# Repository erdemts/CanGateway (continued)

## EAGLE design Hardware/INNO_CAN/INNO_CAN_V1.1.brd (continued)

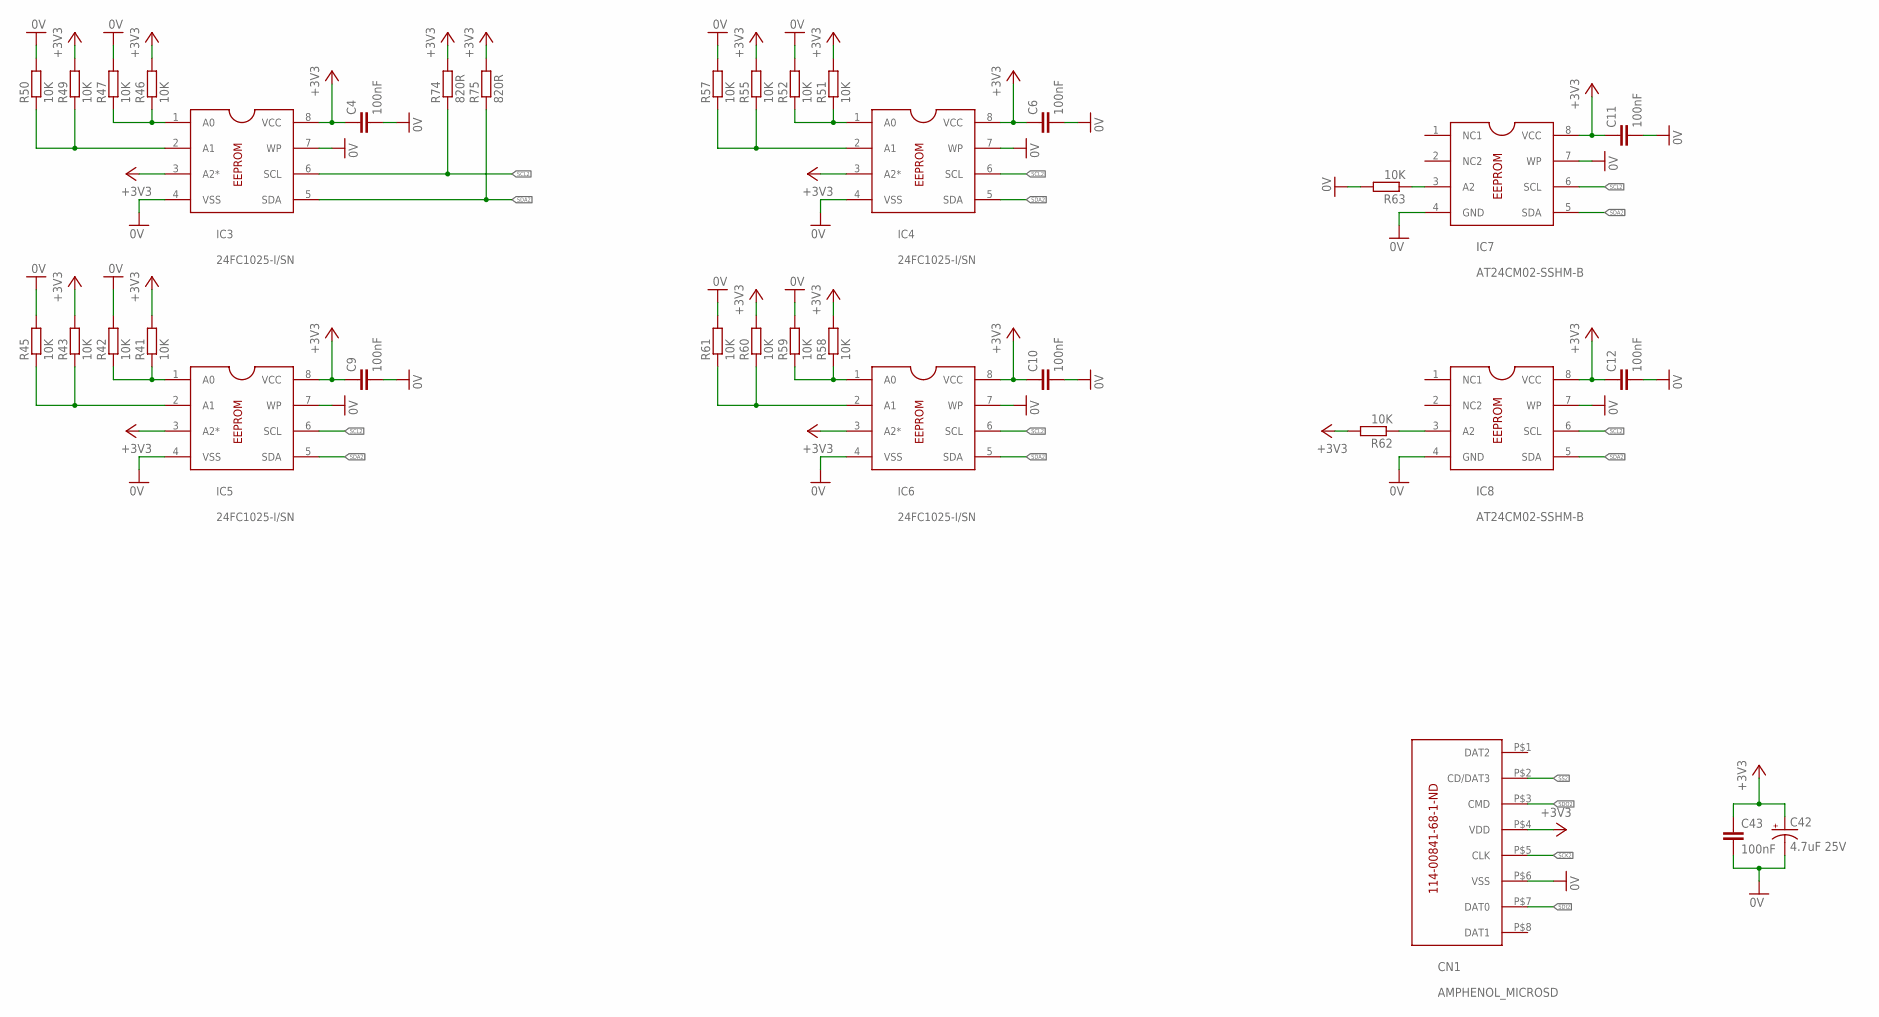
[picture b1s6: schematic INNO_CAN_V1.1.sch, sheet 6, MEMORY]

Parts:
C4, C6, C9, C10, C11, C12, C43: 100nF; C0603
C42: 4.7uF 25V; A/3216-18R
CN1: AMPHENOL_MICROSD
IC3, IC4, IC5, IC6: 24FC1025-I/SN; SOIC08
IC7, IC8: AT24CM02-SSHM-B; SOIC08
R41, R42, R43, R45, R46, R47, R49, R50, R51, R52, R55, R57, R58, R59, R60, R61, R62, R63: 10K; R0603
R74, R75: 820R; R0603

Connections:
0V: C4.2, C6.2, C9.2, C10.2, C11.2, C12.2, C42.-, C43.2, CN1.P$6 (VSS), IC3.4 (VSS), IC3.7 (WP), IC4.4 (VSS), IC4.7 (WP), IC5.4 (VSS), IC5.7 (WP), IC6.4 (VSS), IC6.7 (WP), IC7.4 (GND), IC7.7 (WP), IC8.4 (GND), IC8.7 (WP), R42.2, R45.2, R47.2, R50.2, R52.2, R57.2, R59.2, R61.2, R63.2; also elsewhere on the board
+3V3: C4.1, C6.1, C9.1, C10.1, C11.1, C12.1, C42.+, C43.1, CN1.P$4 (VDD), IC3.3 (A2*), IC3.8 (VCC), IC4.3 (A2*), IC4.8 (VCC), IC5.3 (A2*), IC5.8 (VCC), IC6.3 (A2*), IC6.8 (VCC), IC7.8 (VCC), IC8.8 (VCC), R41.2, R43.2, R46.2, R49.2, R51.2, R55.2, R58.2, R60.2, R62.2, R74.2, R75.2; also elsewhere on the board
unnamed: IC5.1 (A0), R41.1, R42.1
unnamed: IC5.2 (A1), R43.1, R45.1
unnamed: IC3.1 (A0), R46.1, R47.1
unnamed: IC3.2 (A1), R49.1, R50.1
unnamed: IC4.2 (A1), R55.1, R57.1
unnamed: IC4.1 (A0), R51.1, R52.1
unnamed: IC6.1 (A0), R58.1, R59.1
unnamed: IC6.2 (A1), R60.1, R61.1
unnamed: IC8.3 (A2), R62.1
unnamed: IC7.3 (A2), R63.1
SCK2: CN1.P$5 (CLK); also elsewhere on the board
SCL2: IC3.6 (SCL), IC4.6 (SCL), IC5.6 (SCL), IC6.6 (SCL), IC7.6 (SCL), IC8.6 (SCL), R74.1; also elsewhere on the board
SDA2: IC3.5 (SDA), IC4.5 (SDA), IC5.5 (SDA), IC6.5 (SDA), IC7.5 (SDA), IC8.5 (SDA), R75.1; also elsewhere on the board
SDI2: CN1.P$7 (DAT0); also elsewhere on the board
SDO2: CN1.P$3 (CMD); also elsewhere on the board
SS2: CN1.P$2 (CD/DAT3); also elsewhere on the board

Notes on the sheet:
114-00841-68-1-ND

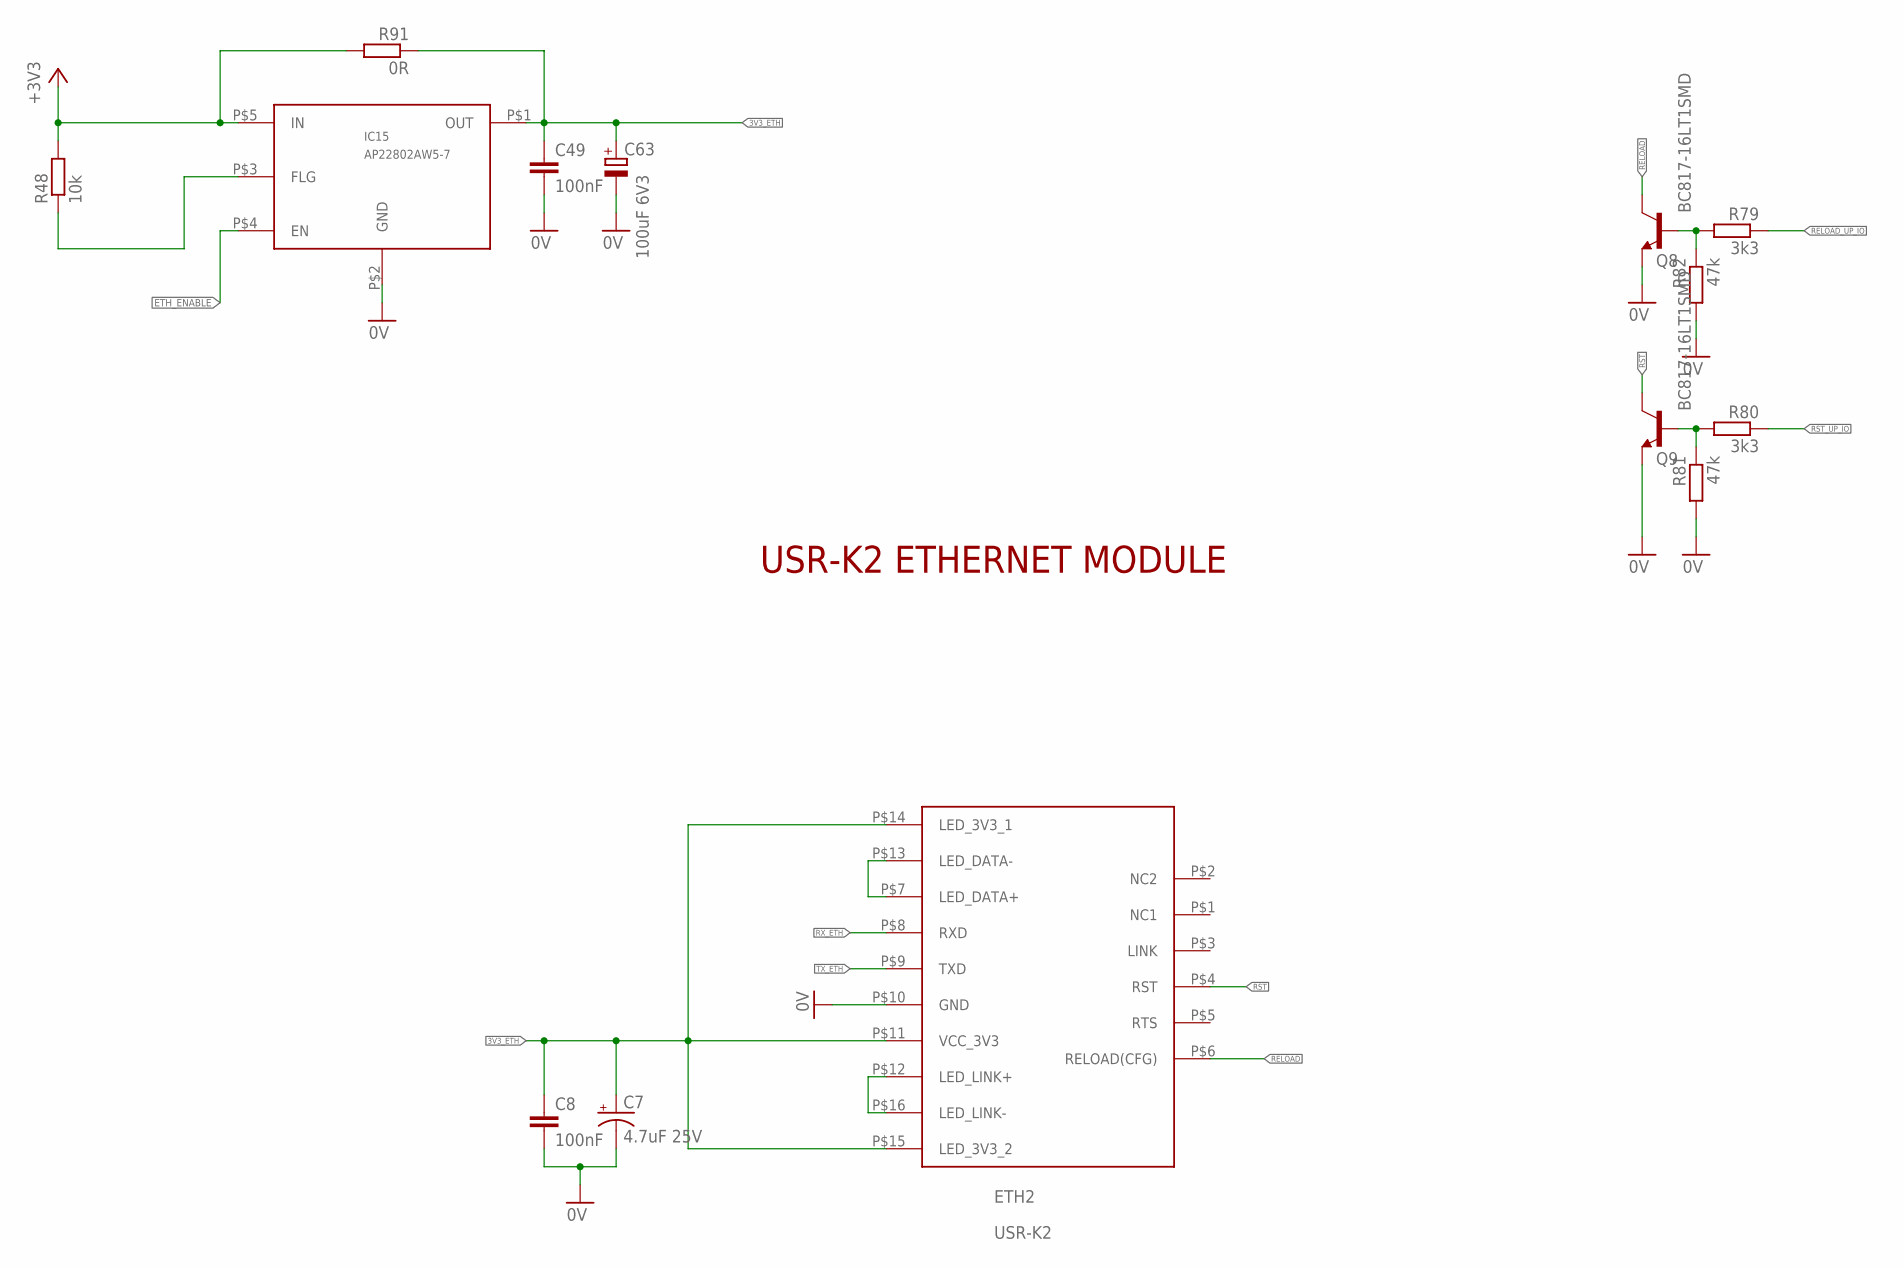
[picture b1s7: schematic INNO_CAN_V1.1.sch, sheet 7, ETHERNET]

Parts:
C7: 4.7uF 25V; A/3216-18R
C8, C49: 100nF; C0603
C63: 100uF 6V3; E5-5
ETH2: USR-K2
IC15: AP22802AW5-7; SOT23-5L
Q8, Q9: BC817-16LT1SMD; SOT23-BEC
R48: 10k; R0603
R79, R80: 3k3; R0805
R81, R82: 47k; R0805
R91: 0R; R0805

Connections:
0V: C7.-, C8.2, C49.2, C63.-, ETH2.P$10 (GND), IC15.P$2 (GND), Q8.E, Q9.E, R81.2, R82.2; also elsewhere on the board
3V3_ETH: C7.+, C8.1, C49.1, C63.+, ETH2.P$11 (VCC_3V3), ETH2.P$14 (LED_3V3_1), ETH2.P$15 (LED_3V3_2), IC15.P$1 (OUT), R91.1
+3V3: IC15.P$5 (IN), R48.2, R91.2; also elsewhere on the board
ETH_ENABLE: IC15.P$4 (EN); also elsewhere on the board
unnamed: ETH2.P$12 (LED_LINK+), ETH2.P$16 (LED_LINK-)
unnamed: ETH2.P$7 (LED_DATA+), ETH2.P$13 (LED_DATA-)
unnamed: IC15.P$3 (FLG), R48.1
RELOAD: ETH2.P$6 (RELOAD(CFG)), Q8.C
RELOAD_UP_IO: R79.1; also elsewhere on the board
RST: ETH2.P$4 (RST), Q9.C
RST_UP_IO: R80.1; also elsewhere on the board
RX_ETH: ETH2.P$8 (RXD); also elsewhere on the board
TXD2: Q8.B, R79.2, R82.1
TXD3: Q9.B, R80.2, R81.1
TX_ETH: ETH2.P$9 (TXD); also elsewhere on the board

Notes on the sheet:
USR-K2 ETHERNET MODULE

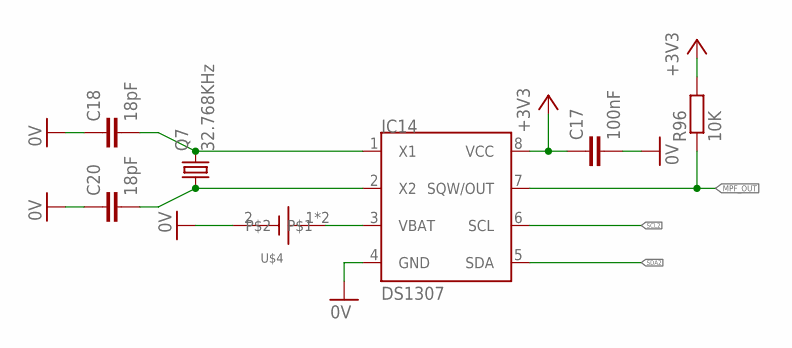
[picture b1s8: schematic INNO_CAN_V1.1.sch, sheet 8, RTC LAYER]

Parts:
C17: 100nF; C0603K
C18, C20: 18pF; C0603
IC14: DS1307; SOIC-8
Q7: 32.768KHz; TC26V
R96: 10K; R0603
U$4: BATTERY

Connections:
0V: C17.2, C18.1, C20.1, IC14.4 (GND), U$4.2; also elsewhere on the board
+3V3: C17.1, IC14.8 (VCC), R96.2; also elsewhere on the board
MPF_OUT: IC14.7 (SQW/OUT), R96.1; also elsewhere on the board
unnamed: C18.2, IC14.1 (X1), Q7.2
unnamed: C20.2, IC14.2 (X2), Q7.1
unnamed: IC14.3 (VBAT), U$4.1, U$4.3
SCL2: IC14.6 (SCL); also elsewhere on the board
SDA2: IC14.5 (SDA); also elsewhere on the board

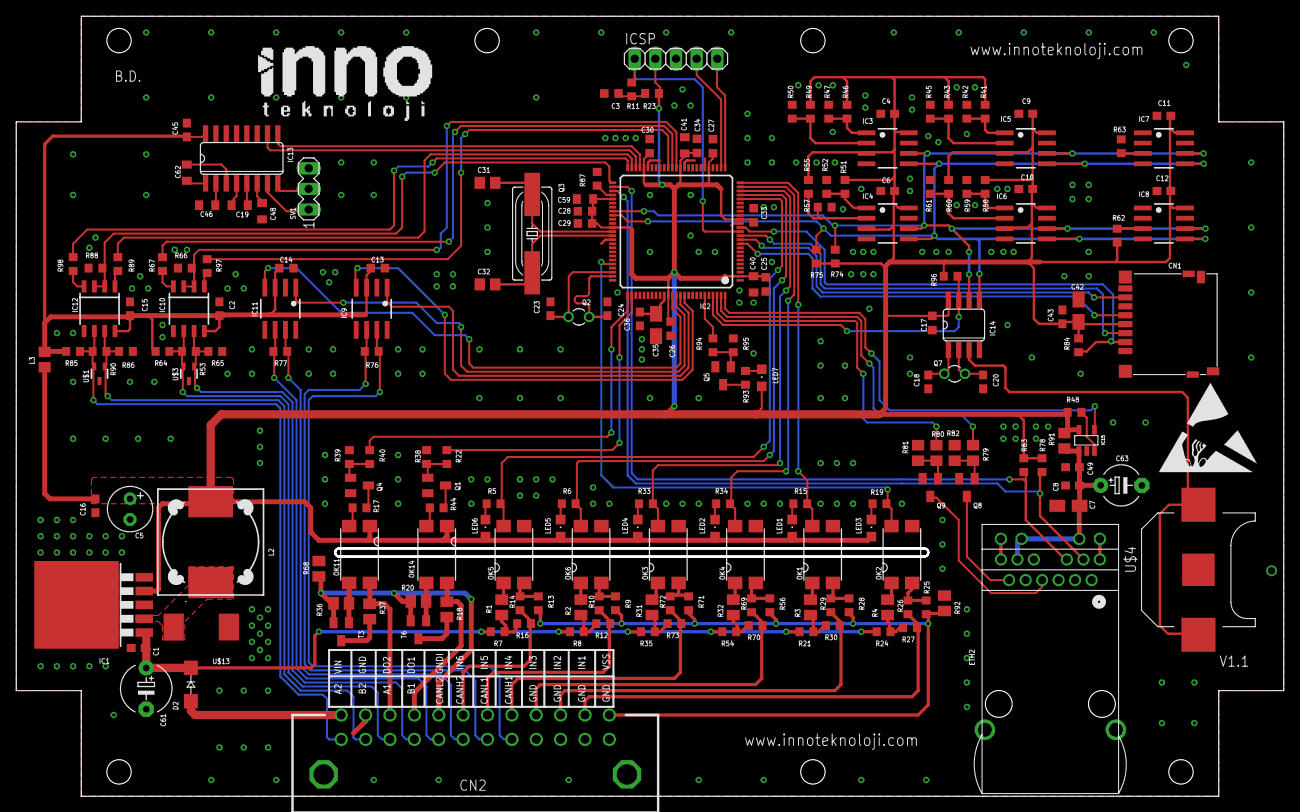
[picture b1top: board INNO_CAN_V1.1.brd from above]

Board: 2 copper layers, 155.7 x 95.7 mm, 196 parts (0 on the bottom side), 137 nets.

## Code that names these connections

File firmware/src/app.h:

/*******************************************************************************
  MPLAB Harmony Application Header File

  Company:
    Microchip Technology Inc.

  File Name:
    app.h

  Summary:
    This header file provides prototypes and definitions for the application.

  Description:
    This header file provides function prototypes and data type definitions for
    the application.  Some of these are required by the system (such as the
    "APP_Initialize" and "APP_Tasks" prototypes) and some of them are only used
    internally by the application (such as the "APP_STATES" definition).  Both
    are defined here for convenience.
 *******************************************************************************/

//DOM-IGNORE-BEGIN
/*******************************************************************************
Copyright (c) 2013-2014 released Microchip Technology Inc.  All rights reserved.

Microchip licenses to you the right to use, modify, copy and distribute
Software only when embedded on a Microchip microcontroller or digital signal
controller that is integrated into your product or third party product
(pursuant to the sublicense terms in the accompanying license agreement).

You should refer to the license agreement accompanying this Software for
additional information regarding your rights and obligations.

SOFTWARE AND DOCUMENTATION ARE PROVIDED "AS IS" WITHOUT WARRANTY OF ANY KIND,
EITHER EXPRESS OR IMPLIED, INCLUDING WITHOUT LIMITATION, ANY WARRANTY OF
MERCHANTABILITY, TITLE, NON-INFRINGEMENT AND FITNESS FOR A PARTICULAR PURPOSE.
IN NO EVENT SHALL MICROCHIP OR ITS LICENSORS BE LIABLE OR OBLIGATED UNDER
CONTRACT, NEGLIGENCE, STRICT LIABILITY, CONTRIBUTION, BREACH OF WARRANTY, OR
OTHER LEGAL EQUITABLE THEORY ANY DIRECT OR INDIRECT DAMAGES OR EXPENSES
INCLUDING BUT NOT LIMITED TO ANY INCIDENTAL, SPECIAL, INDIRECT, PUNITIVE OR
CONSEQUENTIAL DAMAGES, LOST PROFITS OR LOST DATA, COST OF PROCUREMENT OF
SUBSTITUTE GOODS, TECHNOLOGY, SERVICES, OR ANY CLAIMS BY THIRD PARTIES
(INCLUDING BUT NOT LIMITED TO ANY DEFENSE THEREOF), OR OTHER SIMILAR COSTS.
 *******************************************************************************/
//DOM-IGNORE-END

#ifndef _APP_H
#define _APP_H

// *****************************************************************************
// *****************************************************************************
// Section: Included Files
// *****************************************************************************
// *****************************************************************************

#include <stdint.h>
#include <stdbool.h>
#include <stddef.h>
#include <stdlib.h>
#include <time.h>
#include "system_config.h"
#include "system_definitions.h"
#include "IRMA.h"
#include "uart.h"


// DOM-IGNORE-BEGIN
#ifdef __cplusplus  // Provide C++ Compatibility

extern "C" {

#endif
    // DOM-IGNORE-END 

    // *****************************************************************************
    // *****************************************************************************
    // Section: Type Definitions
    // *****************************************************************************
    // *****************************************************************************

#define INPUT_1         PORTBbits.RB0
#define INPUT_2         PORTBbits.RB1
#define INPUT_3         PORTBbits.RB2
#define INPUT_4         PORTBbits.RB3
#define INPUT_5         PORTBbits.RB4
#define INPUT_6         PORTDbits.RD11
#define UART_2_EN       LATFbits.LATF3
#define UART_5_EN       LATAbits.LATA1
#define INPUT_MASK      0b0000000000011111
#define INPUT_PORT      PORTB    

#define bit_set(var,bitno)          ((var) |= 1 << (bitno))
#define bit_clear(var,bitno)        ((var) &= ~(1 << (bitno)))
#define bit_test(data,bitno)        ((data>>bitno)&0x01)
#define hibyte(x)                   (unsigned char)	((x>>8) & 0xFF)
#define lobyte(x)                   (unsigned char)	(x & 0xFF)
#define toShort(HiByte, LoByte)     (unsigned short)(((unsigned short)(HiByte << 8) & 0xFF00) | (unsigned short)LoByte)

    //Device specific defines  
#define MAX_SUPPORTED_SENSOR_COUNT                  4
#define TOTAL_DIGITAL_INPUT                         6  




#define ACTIVE_HIGH                                     1    
#define ACTIVE_LOW                                      0   
#define DOOR_IS_OPEN                                    1       
#define DOOR_IS_CLOSE                                   0    

    typedef enum {
        WAIT_STX = 0,
        WAIT_COMMAND,
        WAIT_LENGHT,
        WAIT_DATA,
        WAIT_CRC_LENGHT,
        WAIT_CRC_H,
        WAIT_CRC_L,
        WAIT_ETX,
        WAIT_ACK,
        RUN_COMMAND
    } COMMAND_HANDLE_STATE;

    typedef enum {
        STATE_SENSOR_IDLE = 0,
        STATE_START_COUNTING,
        STATE_WAIT_DOOR_CLOSING,
        STATE_STOP_COUNTING,
        STATE_WAIT_FA_TIMEOUT,
        STATE_GET_FA_STATUS,
        STATE_GET_COUNT_RESULT,
        STATE_GET_SENSOR_STATUS
    } SENSOR_STATES;

    typedef enum {
        P_STATE_IDLE = 0,
        P_STATE_COUNT_DATA_SEND,
        P_STATE_COUNT_DATA_WAIT_ACK,
        P_STATE_COUNT_DATA_RECORD_EEPROM,
        P_STATE_STATUS_DATA_SEND,
        P_STATE_STATUS_DATA_WAIT_ACK,
        P_STATE_STATUS_DATA_RECORD_EEPROM,
        P_STATE_RECORDED_COUNT_DATA_SEND,
        P_STATE_RECORDED_COUNT_DATA_WAIT_ACK,
        P_STATE_RECORDED_STATUS_DATA_SEND,
        P_STATE_RECORDED_STATUS_DATA_WAIT_ACK
    } DATA_PROCESS_STATES;


    // *****************************************************************************
    // *****************************************************************************
    // Section: Application Initialization and State Machine Functions
    // *****************************************************************************
    // *****************************************************************************

    void APP_Initialize(void);
    void APP_Tasks(void);


    void initializeSystem(void);
    void checkIOProcess(void);
    unsigned short readInputs(void);
    void checkInputsAndChangeSensorStates(unsigned char inputNo);
    void countingProcess(void);
    bool updateSystemTime(unsigned char day, unsigned char month, unsigned char year, unsigned char hour, unsigned char min, unsigned char sec);
    bool updateCoordinates(unsigned char Lat0, unsigned char Lat1, unsigned char Lat2, unsigned char Lat3, unsigned char Lon0, unsigned char Lon1, unsigned char Lon2, unsigned char Lon3);
    time_t getCurrentTime(void);
    void dataProcessManager(void);

    void updateCountDataLogWriteIndexToEEprom(void);
    void updateCountDataLogReadIndexToEEprom(void);
    void updateCountDataIndexFromEEprom(void);
    void updateStatusDataLogWriteIndexToEEprom(void);
    void updateStatusDataLogReadIndexToEEprom(void);
    void updateStatusDataIndexFromEEprom(void);

    void updateSystemParametersFromEEprom(void);
    void recordSystemParametersToEEprom(void);

    void getSensorParameters(unsigned int sensorAddress, volatile IRMA_SENSOR_TYPE* sourceSensors, volatile IRMA_SENSOR_TYPE* destinationSensors);
    void checkAllSensorParameters(void);

    void systemStartupCheck(volatile UART_DATA_TYPE* uartTransmit, volatile UART_DATA_TYPE* uartReceive, unsigned char uartType);

    void fakeInit(void);


#endif /* _APP_H */

    //DOM-IGNORE-BEGIN
#ifdef __cplusplus
}
#endif
//DOM-IGNORE-END

/*******************************************************************************
 End of File
 */
